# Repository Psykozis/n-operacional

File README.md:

# n-operacional
projeto chaveamento de relé
nó ponta para chaveamento

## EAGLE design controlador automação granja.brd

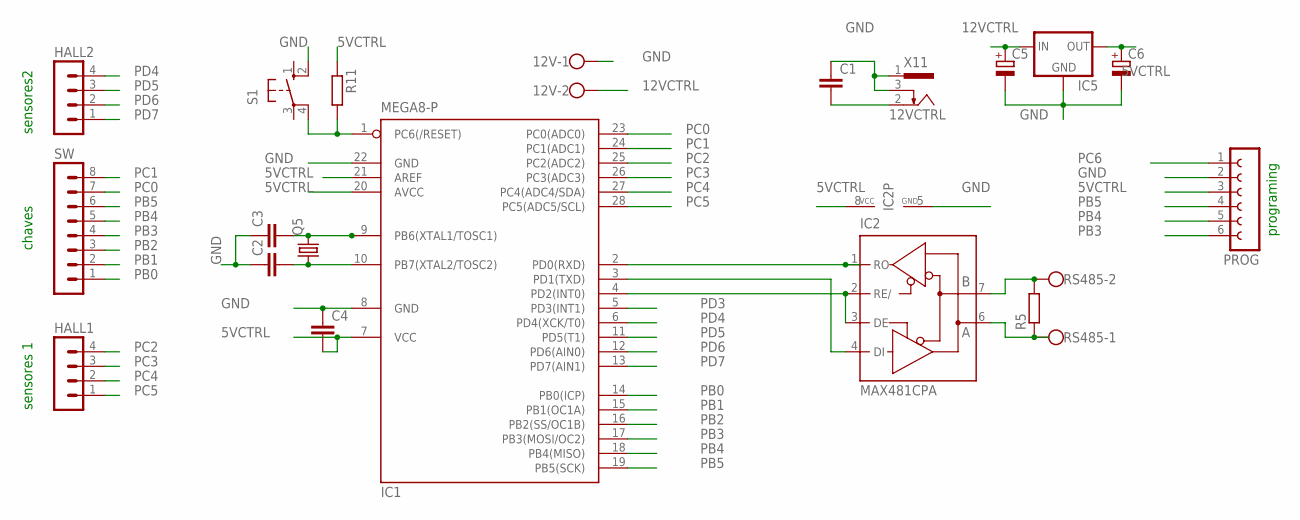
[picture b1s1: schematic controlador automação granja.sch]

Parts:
12V: W237-102
C1, C2: C-EU050-025X075; C050-025X075
C3, C4: C-EU050-024X044; C050-024X044
C5, C6: CPOL-EUE1.8-4; E1,8-4
HALL1, HALL2: MA04-1
IC1: MEGA8-P; DIL28-3
IC2: MAX481CPA; DIL08
IC5: 78LXX
PROG: FE06-1; FE06
Q5: CRYSTALHC49S; HC49/S
R5, R11: R-EU_0207/7; 0207/7
RS485: W237-102
S1: 10-XX; B3F-10XX
SW: MA08-1
X11: 733980-62

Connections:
5VCTRL: C4.2, C6.+, IC1.7 (VCC), IC1.20 (AVCC), IC1.21 (AREF), IC2.8 (VCC), IC5.OUT, PROG.3, R11.1
12VCTRL: 12V.2, C1.2, C5.+, IC5.IN, X11.2
GND: 12V.1, C1.1, C2.1, C3.1, C4.1, C5.-, C6.-, IC1.8 (GND), IC1.22 (GND), IC2.5 (GND), IC5.GND, PROG.2, S1.2 (S1), X11.1, X11.3
unnamed: IC2.7 (B), R5.2, RS485.2
unnamed: IC2.6 (A), R5.1, RS485.1
unnamed: C2.2, IC1.10 (PB7(XTAL2/TOSC2)), Q5.1
unnamed: C3.2, IC1.9 (PB6(XTAL1/TOSC1)), Q5.2
unnamed: IC1.2 (PD0(RXD)), IC2.1 (RO)
unnamed: IC1.3 (PD1(TXD)), IC2.4 (DI)
unnamed: IC1.4 (PD2(INT0)), IC2.2 (RE/), IC2.3 (DE)
PB0: IC1.14 (PB0(ICP)), SW.1
PB1: IC1.15 (PB1(OC1A)), SW.2
PB2: IC1.16 (PB2(SS/OC1B)), SW.3
PB3: IC1.17 (PB3(MOSI/OC2)), PROG.6, SW.4
PB4: IC1.18 (PB4(MISO)), PROG.5, SW.5
PB5: IC1.19 (PB5(SCK)), PROG.4, SW.6
PC0: IC1.23 (PC0(ADC0)), SW.7
PC1: IC1.24 (PC1(ADC1)), SW.8
PC2: HALL1.4, IC1.25 (PC2(ADC2))
PC3: HALL1.3, IC1.26 (PC3(ADC3))
PC4: HALL1.2, IC1.27 (PC4(ADC4/SDA))
PC5: HALL1.1, IC1.28 (PC5(ADC5/SCL))
PC6: IC1.1 (PC6(/RESET)), PROG.1, R11.2, S1.4 (P1)
PD3: IC1.5 (PD3(INT1))
PD4: HALL2.4, IC1.6 (PD4(XCK/T0))
PD5: HALL2.3, IC1.11 (PD5(T1))
PD6: HALL2.2, IC1.12 (PD6(AIN0))
PD7: HALL2.1, IC1.13 (PD7(AIN1))

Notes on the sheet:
programing
chaves
sensores 1
sensores2

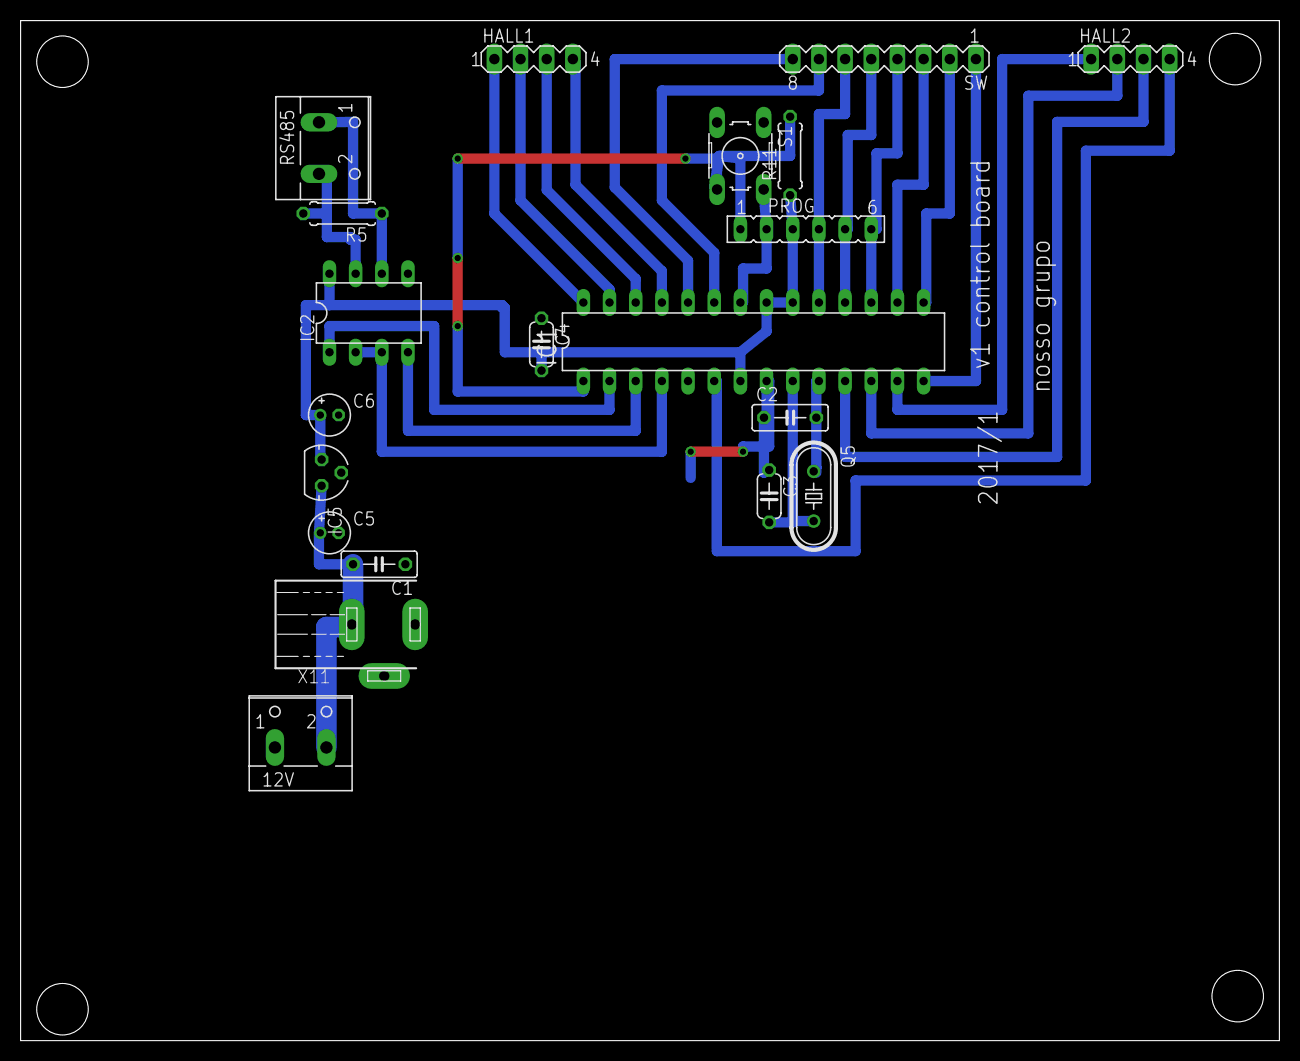
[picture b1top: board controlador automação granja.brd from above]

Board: 2 copper layers, 122.2 x 99.0 mm, 20 parts (0 on the bottom side), 27 nets.

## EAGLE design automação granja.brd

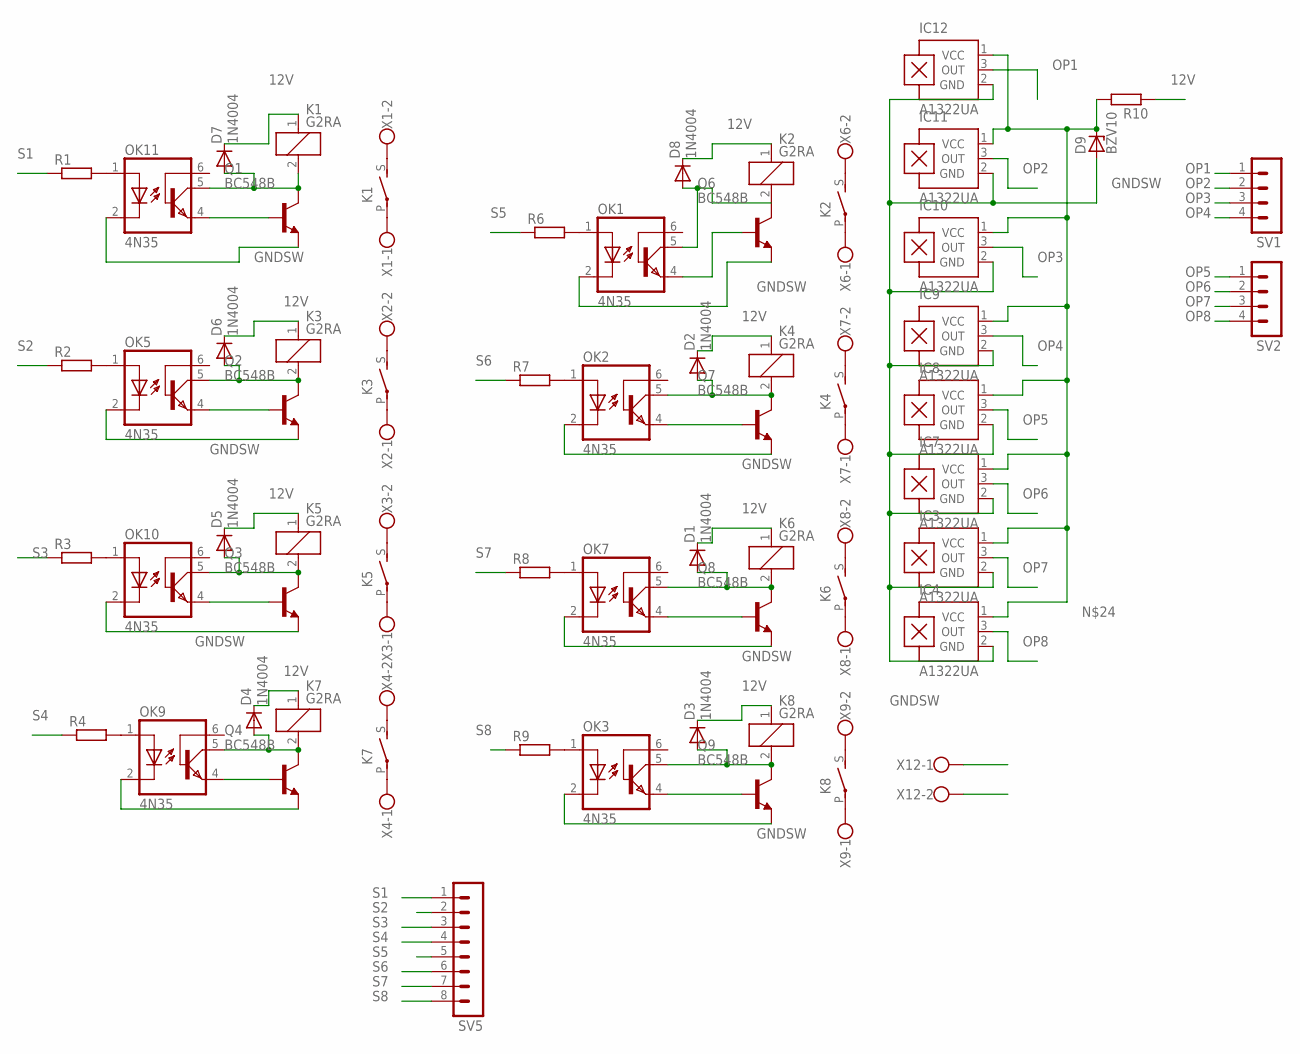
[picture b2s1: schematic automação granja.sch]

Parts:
D1, D2, D3, D4, D5, D6, D7, D8: 1N4004; DO41-10
D9: BZV10; DO34Z7
IC3, IC4, IC7, IC8, IC9, IC10, IC11, IC12: A1322UA; SIP3-UA
K1, K2, K3, K4, K5, K6, K7, K8: G2RA
OK1, OK2, OK3, OK5, OK7, OK9, OK10, OK11: 4N35; DIL06
Q1, Q2, Q3, Q4, Q6, Q7, Q8, Q9: BC548B; TO92-EBC
R1, R2, R3, R4, R6, R7, R8, R9, R10: R-EU_0207/7; 0207/7
SV1, SV2: MA04-1
SV5: MA08-1
X1, X2, X3, X4, X6, X7, X8, X9, X12: W237-102

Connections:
12V: D1.C, D2.C, D3.C, D4.C, D5.C, D6.C, D7.C, D8.C, K1.1, K2.1, K3.1, K4.1, K5.1, K6.1, K7.1, K8.1, R10.1, X12.1
GNDSW: D9.A, IC3.2 (GND), IC4.2 (GND), IC7.2 (GND), IC8.2 (GND), IC9.2 (GND), IC10.2 (GND), IC11.2 (GND), IC12.2 (GND), OK1.2 (C), OK2.2 (C), OK3.2 (C), OK5.2 (C), OK7.2 (C), OK9.2 (C), OK10.2 (C), OK11.2 (C), Q1.E, Q2.E, Q3.E, Q4.E, Q6.E, Q7.E, Q8.E, Q9.E, X12.2
unnamed: D7.A, K1.2, OK11.5 (COL), Q1.C
unnamed: K1.S, X1.2
unnamed: K1.P, X1.1
unnamed: D6.A, K3.2, OK5.5 (COL), Q2.C
unnamed: K3.S, X2.2
unnamed: K3.P, X2.1
unnamed: K5.S, X3.2
unnamed: K5.P, X3.1
unnamed: D5.A, K5.2, OK10.5 (COL), Q3.C
unnamed: K7.S, X4.2
unnamed: K7.P, X4.1
unnamed: OK1.1 (A), R6.2
unnamed: OK1.4 (EMI), Q6.B
unnamed: OK2.4 (EMI), Q7.B
unnamed: D4.A, K7.2, OK9.5 (COL), Q4.C
unnamed: OK7.4 (EMI), Q8.B
unnamed: OK3.4 (EMI), Q9.B
unnamed: D8.A, K2.2, OK1.5 (COL), Q6.C
unnamed: K2.S, X6.2
unnamed: K2.P, X6.1
unnamed: D9.C, IC3.1 (VCC), IC4.1 (VCC), IC7.1 (VCC), IC8.1 (VCC), IC9.1 (VCC), IC10.1 (VCC), IC11.1 (VCC), IC12.1 (VCC), R10.2
unnamed: D2.A, K4.2, OK2.5 (COL), Q7.C
unnamed: K4.S, X7.2
unnamed: K4.P, X7.1
unnamed: K6.S, X8.2
unnamed: K6.P, X8.1
unnamed: D1.A, K6.2, OK7.5 (COL), Q8.C
unnamed: OK2.1 (A), R7.2
unnamed: OK7.1 (A), R8.2
unnamed: K8.S, X9.2
unnamed: K8.P, X9.1
unnamed: D3.A, K8.2, OK3.5 (COL), Q9.C
unnamed: OK3.1 (A), R9.2
unnamed: OK11.1 (A), R1.2
unnamed: OK5.1 (A), R2.2
unnamed: OK10.1 (A), R3.2
unnamed: OK9.1 (A), R4.2
unnamed: OK5.4 (EMI), Q2.B
unnamed: OK10.4 (EMI), Q3.B
unnamed: OK9.4 (EMI), Q4.B
unnamed: OK11.4 (EMI), Q1.B
OP1: IC12.3 (OUT), SV1.1
OP2: IC11.3 (OUT), SV1.2
OP3: IC10.3 (OUT), SV1.3
OP4: IC9.3 (OUT), SV1.4
OP5: IC8.3 (OUT), SV2.1
OP6: IC7.3 (OUT), SV2.2
OP7: IC3.3 (OUT), SV2.3
OP8: IC4.3 (OUT), SV2.4
S1: R1.1, SV5.1
S2: R2.1, SV5.2
S3: R3.1, SV5.3
S4: R4.1, SV5.4
S5: R6.1, SV5.5
S6: R7.1, SV5.6
S7: R8.1, SV5.7
S8: R9.1, SV5.8

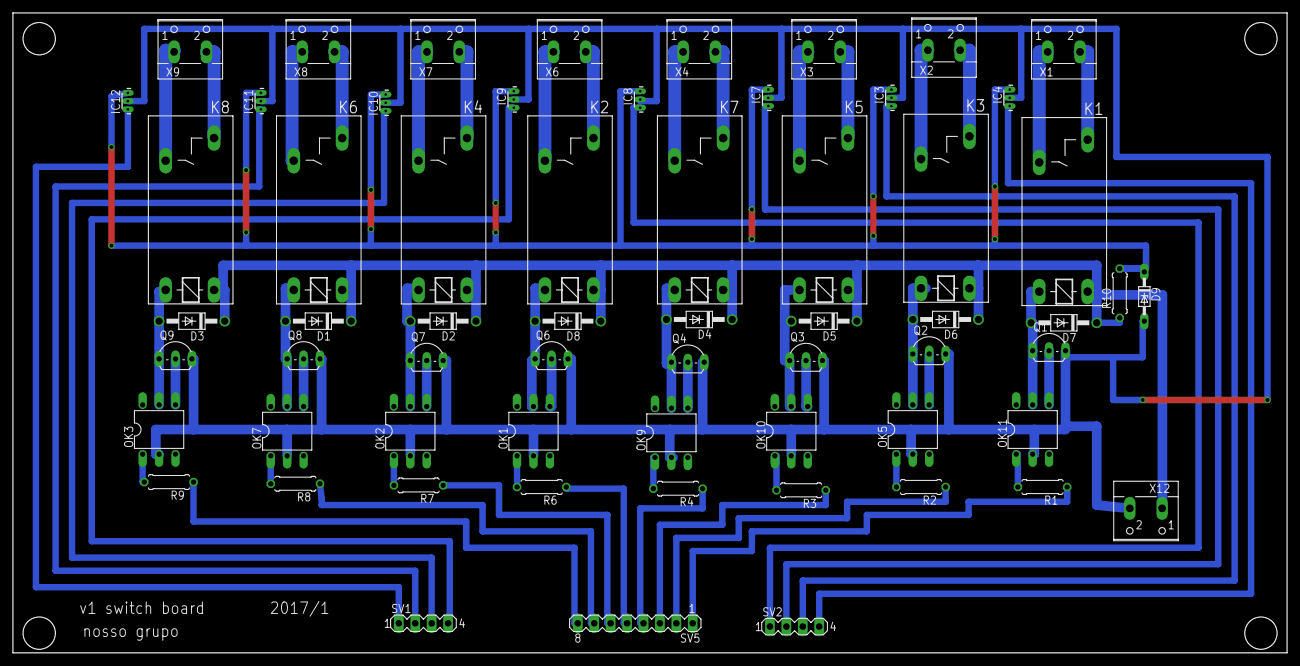
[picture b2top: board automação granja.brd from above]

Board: 2 copper layers, 197.1 x 99.0 mm, 62 parts (0 on the bottom side), 59 nets.

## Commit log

2017-02-17 eagle
2017-02-20 separadas controle de atuação e realimentação
